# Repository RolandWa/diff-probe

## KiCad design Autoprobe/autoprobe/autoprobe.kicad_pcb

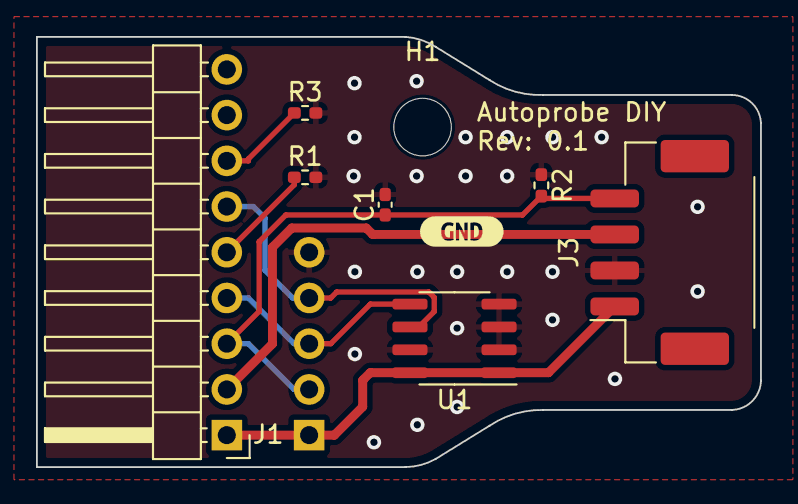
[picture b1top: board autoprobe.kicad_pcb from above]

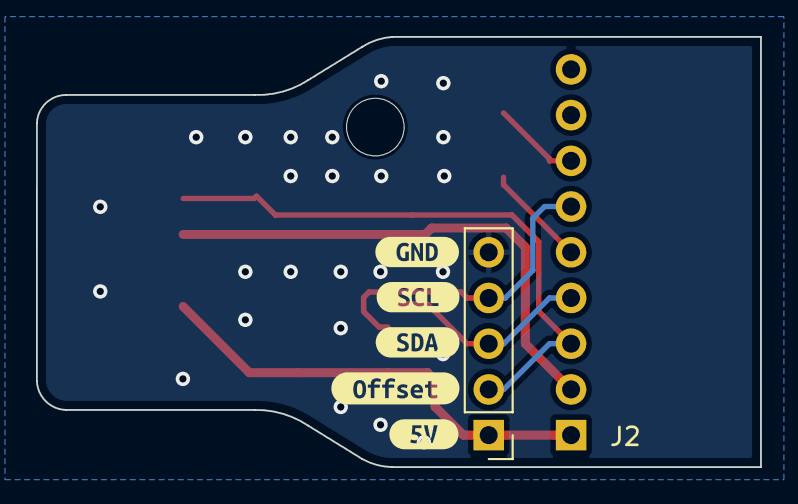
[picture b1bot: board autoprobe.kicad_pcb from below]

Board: 2 copper layers, 40.2 x 23.9 mm, 15 parts (6 on the bottom side), 8 nets.

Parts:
C1: 100nF; C_0402_1005Metric_Pad0.74x0.62mm_HandSolder
H1: MountingHole; MountingHole_3.2mm_M3
J1: Conn_01x09; PinHeader_1x09_P2.54mm_Horizontal
J2: Conn_01x05; PinHeader_1x05_P2.54mm_Vertical
J3: Molex 502494-0470; Molex_CLIK-Mate_502494-0470_1x04-1MP_P2.00mm_Horizontal
R1: 46.4k; R_0402_1005Metric_Pad0.72x0.64mm_HandSolder
R2: 4k7; R_0402_1005Metric_Pad0.72x0.64mm_HandSolder
R3: 10k; R_0402_1005Metric_Pad0.72x0.64mm_HandSolder
U1: M24C02-FMN; SOIC-8_3.9x4.9mm_P1.27mm
kibuzzard-63088BD7: G***; kibuzzard-63088BD7
kibuzzard-63088BFC: G***; kibuzzard-63088BFC
kibuzzard-63088C13: G***; kibuzzard-63088C13
kibuzzard-63088C22: G***; kibuzzard-63088C22
kibuzzard-63088F9B: G***; kibuzzard-63088F9B
kibuzzard-63088F52: G***; kibuzzard-63088F52

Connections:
+5V: J1.1, J2.1, J3.1, U1.1 (E0), U1.8 (VCC)
-5V: J1.2, J3.3
GND: C1.2, J2.5, J3.2, R1.2, R2.1, R3.2, U1.2 (E1), U1.3 (E2), U1.4 (VSS), U1.7 (~WC)
unnamed: J1.5, R1.1
unnamed: J1.7, R3.1
Offset: C1.1, J1.3, J2.2, J3.4, R2.2
SCL: J1.6, J2.4, U1.6 (SCL)
SDA: J1.4, J2.3, U1.5 (SDA)

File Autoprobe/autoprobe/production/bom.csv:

Designator,Footprint,Quantity,Value,LCSC Part #
C1,0402,1,100nF,
H1,MountingHole_3.2mm_M3,1,MountingHole,
J1,PinHeader_1x09_P2.54mm_Horizontal,1,Conn_01x09,
J2,PinHeader_1x05_P2.54mm_Vertical,1,Conn_01x05,
J3,Molex_CLIK-Mate_502494-0470_1x04-1MP_P2.00mm_Horizontal,1,Molex 502494-0470,
R1,0402,1,46.4k,
R2,0402,1,4k7,
R3,0402,1,10k,
U1,SOIC-8_3.9x4.9mm_P1.27mm,1,M24C02-FMN,

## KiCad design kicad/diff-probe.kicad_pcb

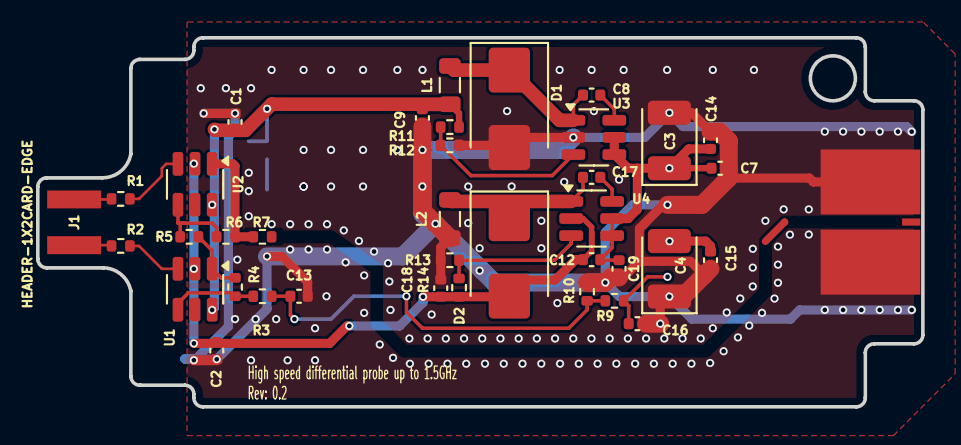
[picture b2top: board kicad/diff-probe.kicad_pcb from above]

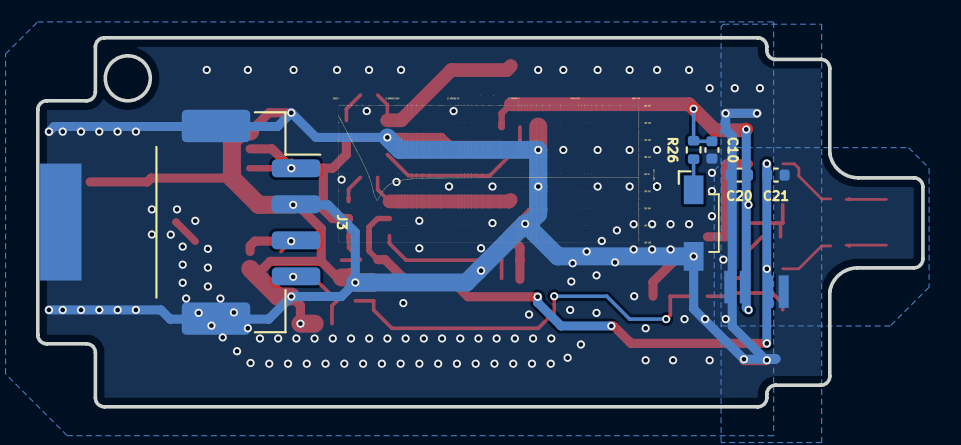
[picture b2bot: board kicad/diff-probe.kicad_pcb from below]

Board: 2 copper layers, 49.2 x 20.5 mm, 47 parts (9 on the bottom side), 23 nets.

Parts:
C1, C2, C10, C16, C20, C21: 100nF; C_0402_1005Metric
C3, C4: 22uF; CP_EIA-3528-21_Kemet-B
C5, C6: 100nF; C_0306_0816Metric
C7, C19: 10uF/16V; C_0402_1005Metric
C8, C17: 10nF; C_0402_1005Metric
C9, C18: 10uF/6.3V; C_0402_1005Metric
C12, C14, C15: 1µF; C_0402_1005Metric
C13: 1nF; C_0402_1005Metric
D1, D2: SS13A; D_SMB
D3: OSM44008C1F; LED_OptoSupply_OSXX4008C1F_4x1.4mm_Horizontal
G_Bandwidth : LOGO
J1: HEADER-1X2CARD-EDGE; CARD_EDGE_PADS-1X2
J3: Molex 502494-0470; Molex_CLIK-Mate_502494-0470_1x04-1MP_P2.00mm_Horizontal
J4: 901-10511-3
L1, L2: 4.7uH; L_0805_2012Metric
R1: 100Ω; R_0402_1005Metric
R2: 100; R_0402_1005Metric
R3, R4, R5, R6, R10: 1kΩ; R_0402_1005Metric
R7: 10Ω; R_0402_1005Metric
R9: 99kΩ; R_0402_1005Metric
R11, R13: 24kΩ; R_0402_1005Metric
R12, R14: 4.7kΩ; R_0402_1005Metric
R26: 1k; R_0402_1005Metric
U1, U2: OPA847xDBV; SOT-23-6
U3, U4: AP3211K; SOT-23-6

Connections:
/IN_N: R2.2, U1.3 (+)
/IN_P: R1.2, U2.3 (+)
/OUT: R6.2, R7.1, U2.1
/OutPad: J4.1, R7.2
/Pad_N: J1.P$2 (2), R2.1
/Pad_P: J1.P$1 (1), R1.1
/Power_supply/IN_N: C4.2, C15.2, J3.3
/Power_supply/IN_P: C3.1, C7.1, C12.1, C14.1, C19.1, J3.1, U3.4 (EN), U3.5 (IN), U4.4 (EN), U4.5 (IN)
/Power_supply/V+: C1.1, C6.1, C9.1, C10.1, C20.1, L1.2, R11.1, R26.2, U1.6 (V+), U2.6 (V+)
/Power_supply/V-: C2.2, C5.2, C12.2, C18.2, C21.2, D2.2 (A), R14.2, U1.2 (V-), U2.2 (V-), U4.2 (GND)
/offset: C16.1, J3.4, R9.1
/offset_prec: C13.1, R3.1, R9.2, R10.1
GND: C1.2, C2.1, C3.2, C4.1, C5.1, C6.2, C7.2, C9.2, C10.2, C13.2, C14.2, C15.1, C16.2, C18.1, C19.2, C20.2, C21.1, D1.2 (A), D3.1 (K), J3.2, J3.MP, J4.2, L2.2, R10.2, R12.2, R13.1, U3.2 (GND)
unnamed: C8.2, D1.1 (K), L1.1, U3.1 (BS)
unnamed: C17.2, D2.1 (K), L2.1, U4.1 (BS)
unnamed: D3.2 (A), R26.1
unnamed: R4.2, R5.1, U1.1
unnamed: R3.2, R4.1, U1.4 (-)
unnamed: R5.2, R6.1, U2.4 (-)
unnamed: R11.2, R12.1, U3.3 (FB)
unnamed: C8.1, U3.6 (SW)
unnamed: R13.2, R14.1, U4.3 (FB)
unnamed: C17.1, U4.6 (SW)

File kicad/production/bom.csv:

Designator,Footprint,Quantity,Value,LCSC Part #
"C1, C10, C2, C20, C21",0402,5,100nF,
"C12, C14, C15",0402,3,1µF,C52923
C13,0402,1,1nF,
C16,0402,1,100nF,C15195
"C17, C8",0402,2,10nF,
"C18, C9",0402,2,10uF/6.3V,
"C19, C7",0402,2,10uF/16V,
"C3, C4",CP_EIA-3528-21_Kemet-B,2,22uF,C1957193
"C5, C6",0306,2,100nF,C2171054
"D1, D2",D_SMB,2,SS13A,
D3,LED_OptoSupply_OSXX4008C1F_4x1.4mm_Horizontal,1,OSM44008C1F,
J1,CARD_EDGE_PADS-1X2,1,HEADER-1X2CARD-EDGE,
J3,Molex_CLIK-Mate_502494-0470_1x04-1MP_P2.00mm_Horizontal,1,Molex 502494-0470,
J4,901-10511-3,1,901-10511-3,C5928875
"L1, L2",0805,2,4.7uH,
R1,0402,1,100Ω,C25082
R10,0402,1,1kΩ,C477760
"R11, R13",0402,2,24kΩ,C477760
"R12, R14",0402,2,4.7kΩ,C477760
R2,0402,1,100,C25082
R26,0402,1,1k,
"R3, R4, R5, R6",0402,4,1kΩ,C25091
R7,0402,1,10Ω,C477760
R9,0402,1,99kΩ,C477760
"U1, U2",SOT-23-6,2,OPA847xDBV,
"U3, U4",SOT-23-6,2,AP3211K,

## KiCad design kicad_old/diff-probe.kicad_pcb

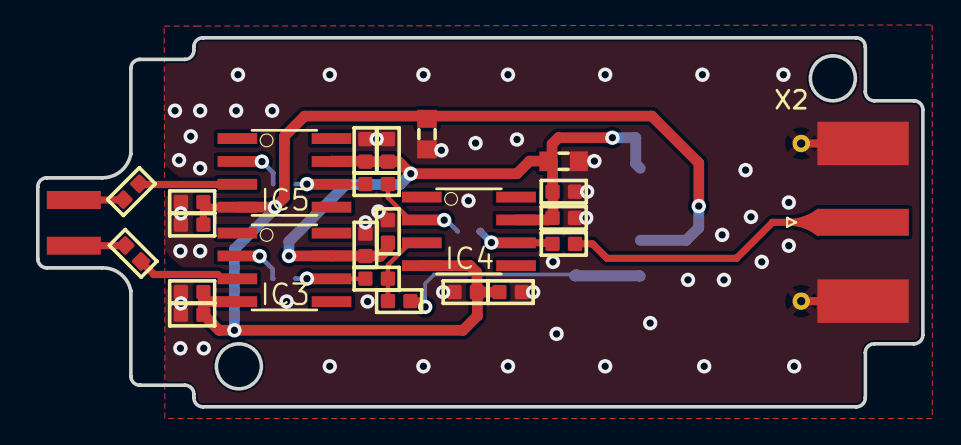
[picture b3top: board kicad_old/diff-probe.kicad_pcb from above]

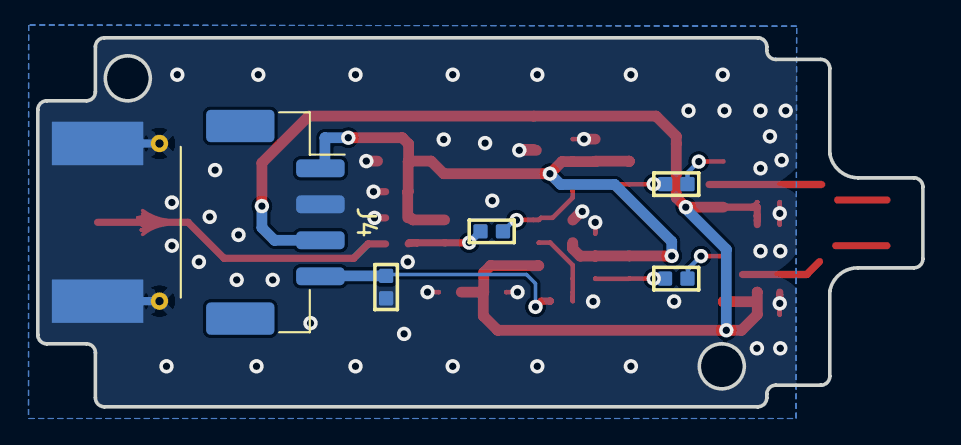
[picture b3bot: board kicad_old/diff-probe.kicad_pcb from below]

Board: 2 copper layers, 49.2 x 20.5 mm, 30 parts (5 on the bottom side), 16 nets.

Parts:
C1, C13, C14, C15, C16, C17, C18, C19, C20, C21, C22, C23, C24: 100nF; 0402-SQUARE
C52, C54: 1µF; 0603
IC3, IC4, IC5: LMH6702; SO08
J3: HEADER-1X2CARD-EDGE; CARD_EDGE_PADS-1X2
J4: Molex 502494-0470; Molex_CLIK-Mate_502494-0470_1x04-1MP_P2.00mm_Horizontal
R20, R28: 150Ω; 0402-SQUARE
R22, R32: 1.1kΩ; 0402-SQUARE
R26, R27, R37, R38: 220Ω; 0402-SQUARE
R30: 50Ω; 0402-SQUARE
X2: SMA--BU-SMA-H; SMA_Molex_73251-1153_EdgeMount_Horizontal_new

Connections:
/NEGIN: IC5.3 (+IN), R28.P$2 (2)
/NEGMID: IC4.2 (-IN), R32.P$2 (2), R38.P$1 (1)
/NegIn1: IC5.6 (OUT), R32.P$1 (1), R37.P$2 (2)
/NegPad: J3.P$2 (2), R28.P$1 (1)
/OUT: IC4.6 (OUT), R30.P$1 (1), R38.P$2 (2)
/OutPad: R30.P$2 (2), X2.1
/POSIN: IC3.3 (+IN), R20.P$2 (2)
/POSMID: IC4.3 (+IN), R22.P$2 (2), R26.P$1 (1)
/PosIn1: IC3.6 (OUT), R22.P$1 (1), R27.P$2 (2)
/PosPad: J3.P$1 (1), R20.P$1 (1)
/offset: C1.P$1 (1), J4.4, R26.P$2 (2)
GND: C1.P$2 (2), C13.P$2 (2), C14.P$2 (2), C15.P$2 (2), C16.P$2 (2), C17.P$2 (2), C18.P$2 (2), C19.P$1 (1), C20.P$1 (1), C21.P$1 (1), C22.P$1 (1), C23.P$1 (1), C24.P$1 (1), C52.2, C54.1, J4.2, X2.2
unnamed: IC3.2 (-IN), R27.P$1 (1)
unnamed: IC5.2 (-IN), R37.P$1 (1)
V+: C13.P$1 (1), C14.P$1 (1), C15.P$1 (1), C16.P$1 (1), C17.P$1 (1), C18.P$1 (1), C52.1, IC3.7 (+VS1), IC4.7 (+VS1), IC5.7 (+VS1), J4.1
V-: C19.P$2 (2), C20.P$2 (2), C21.P$2 (2), C22.P$2 (2), C23.P$2 (2), C24.P$2 (2), C54.2, IC3.4 (-VS1), IC4.4 (-VS1), IC5.4 (-VS1), J4.3

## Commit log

2025-04-30 Change name for the old project to the kicad_old, remove old stored files. Create new design use new faster op-amp, and two op-amp differential input, create simulation for it. Update PCB design. Sti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
2025-05-14 Update schematic using the new version of Op-amp, with high bandwidth, new topology, new DC/DC converter to create 5V power supply from 15V, and negative -5V from it.
2025-05-14 New version at the end of the day.
2025-05-16 Update project. Route signals, make a coplanar 50 R output - two layer board.
2025-05-19 1. Update project regarding to the clean up the rules for the https://jlcpcb.com/ 2. Make the output as Co-planar Wave-guide 50 Ohm 3. Trim the differential input length, and width
2025-05-21 Update Autoprobe project to the Kicad 9.xx Add some Bin files for the EEPROM data add some documentation files
    Update the High speed diff probe Kicad data
    change the silkscreen - more reasonable position
    Add the Project Name, an revision on the PCB board.
